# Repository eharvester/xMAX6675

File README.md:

# xMAX6675

Another MAX6675 library for Arduino

Allows multiple MAX6675 thermocouple controllers on a Arduino/ATMEGA. Uses SPI at maximum possible speed for efficiency. Please check the example.

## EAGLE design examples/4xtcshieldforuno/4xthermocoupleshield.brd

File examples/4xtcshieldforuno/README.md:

# 4x Thermocouple Shield for Arduino Uno 

## Compile and upload (Linux):

### 1) set the following environment variables:

`PATH_TO_ARDUINO_IDE = /path/to/your/arduinoIDE`

`ARDUINO_IDE_VER = 1.6.X` (or what your version is)

`GITHUB_MIRROR = /path/to/your/github/mirror` (optional, local github mirror, https://github.com is used per default)

### 2) connect Arduino Uno to PC via USB cable

### 3) execute the following commands:

`$make`

`$make upload`

`$make minicom`

Make sure you have write permissions to `/dev/ttyUSB0`.

## Hardware

PCB can be build with [toner transfer method](http://www.instructables.com/id/Cheap-and-Easy-Toner-Transfer-for-PCB-Making) easily. Only bottom layer needs to be etched, use wires for top layer.

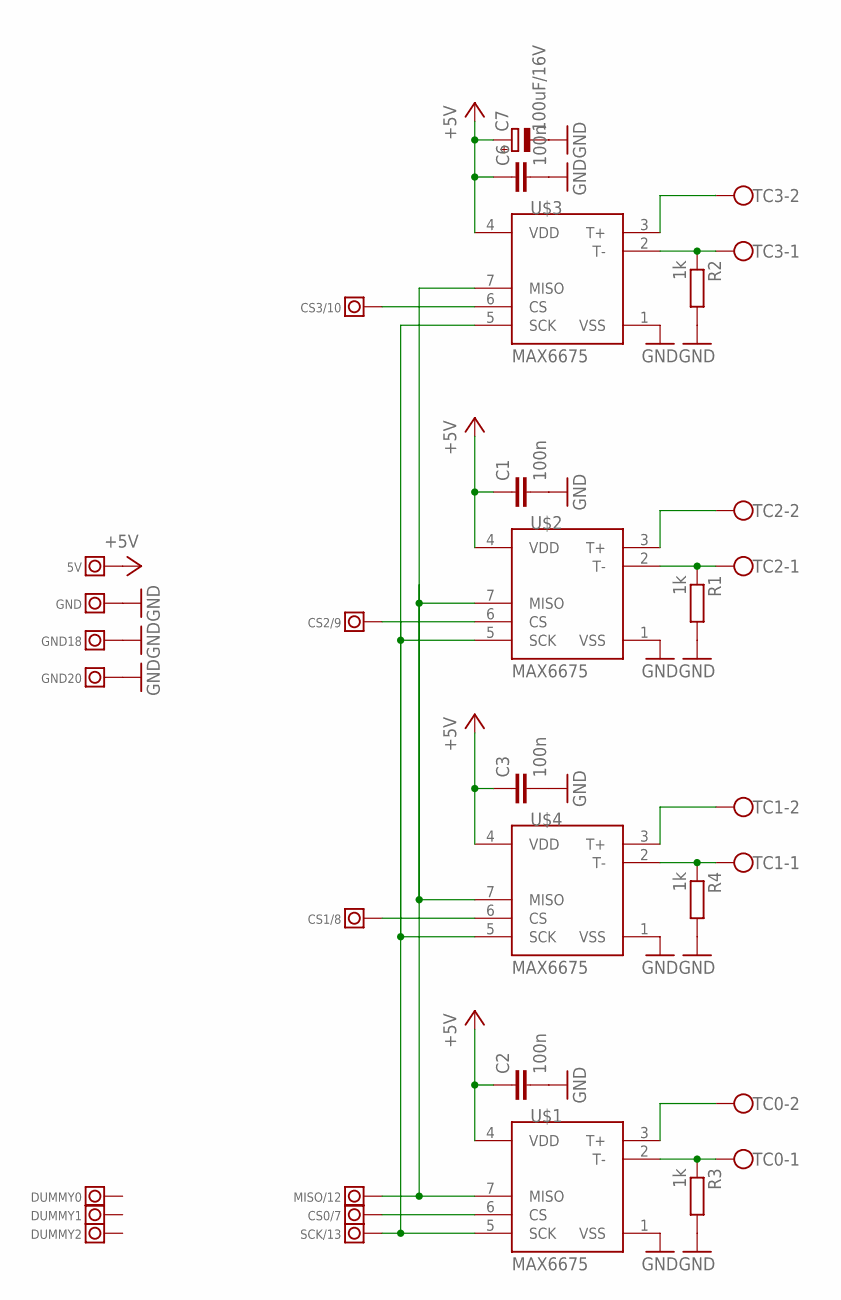
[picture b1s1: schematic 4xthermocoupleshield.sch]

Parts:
5V: PIN-HEADER; PIN-HEADER-MALE
C1, C2, C3, C6: 100n; C0603
C7: 100uF/16V; E2,5-7
CS0/7, CS1/8, CS2/9, CS3/10: PIN-HEADER; PIN-HEADER-MALE
DUMMY0, DUMMY1, DUMMY2: PIN-HEADER; PIN-HEADER-MALE
GND, GND18, GND20: PIN-HEADER; PIN-HEADER-MALE
MISO/12: PIN-HEADER; PIN-HEADER-MALE
R1, R2, R3, R4: 1k; R0603
SCK/13: PIN-HEADER; PIN-HEADER-MALE
TC0, TC1, TC2, TC3: W237-102
U$1, U$2, U$3, U$4: MAX6675; SO08-MAX6675

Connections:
+5V: 5V.P$1, C1.1, C2.1, C3.1, C6.1, C7.+, U$1.4 (VDD), U$2.4 (VDD), U$3.4 (VDD), U$4.4 (VDD)
GND: C1.2, C2.2, C3.2, C6.2, C7.-, GND.P$1, GND18.P$1, GND20.P$1, R1.2, R2.2, R3.2, R4.2, U$1.1 (VSS), U$2.1 (VSS), U$3.1 (VSS), U$4.1 (VSS)
unnamed: TC0.2, U$1.3 (T+)
unnamed: R1.1, TC2.1, U$2.2 (T-)
unnamed: TC2.2, U$2.3 (T+)
unnamed: CS2/9.P$1, U$2.6 (CS)
unnamed: R2.1, TC3.1, U$3.2 (T-)
unnamed: MISO/12.P$1, U$1.7 (MISO), U$2.7 (MISO), U$3.7 (MISO), U$4.7 (MISO)
unnamed: R3.1, TC0.1, U$1.2 (T-)
unnamed: CS0/7.P$1, U$1.6 (CS)
unnamed: SCK/13.P$1, U$1.5 (SCK), U$2.5 (SCK), U$3.5 (SCK), U$4.5 (SCK)
unnamed: TC3.2, U$3.3 (T+)
unnamed: R4.1, TC1.1, U$4.2 (T-)
unnamed: CS3/10.P$1, U$3.6 (CS)
unnamed: TC1.2, U$4.3 (T+)
unnamed: CS1/8.P$1, U$4.6 (CS)

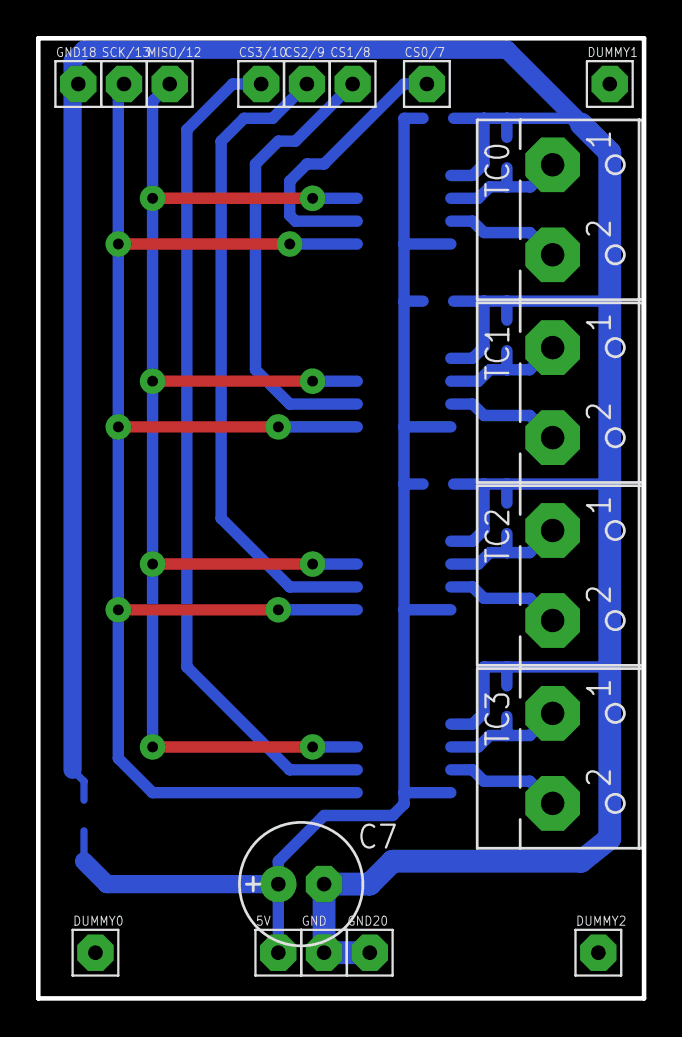
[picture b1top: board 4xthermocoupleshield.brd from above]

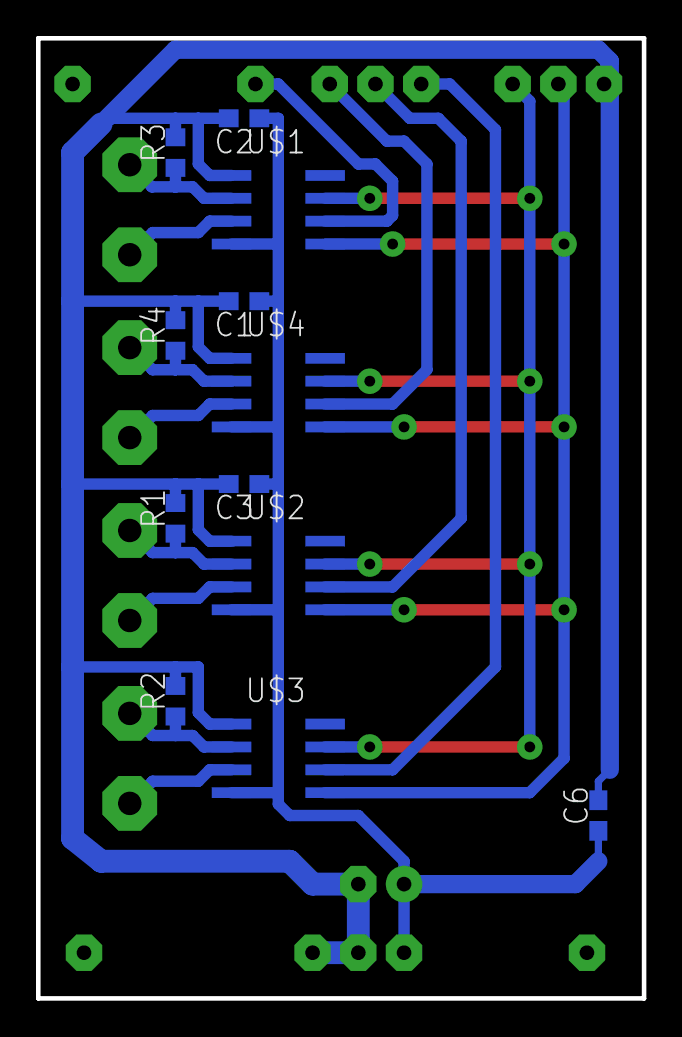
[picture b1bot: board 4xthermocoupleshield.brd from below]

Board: 2 copper layers, 33.7 x 53.3 mm, 30 parts (12 on the bottom side), 16 nets.

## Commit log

2016-04-26 Fix repository eharvest -> eharvester
2016-04-29 adding picture
2016-04-29 inserting picture
2016-04-29 formatting, link
2016-04-29 formatting
2018-07-22 Rename example sketch file to match folder name
    The Arduino IDE requires the sketch folder name to match the filename of the primary sketch file. This change causes the example sketch to be accessible via the Arduino IDE's File > Examples > LIBRAR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

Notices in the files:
parts and their libraries:
SparkFun-AnalogIC: Licensing:Creative Commons ShareAlike 4.0 International - https://creativecommons.org/licenses/by-sa/4.0
